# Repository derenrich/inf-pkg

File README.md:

# E-Ink RP2040 Driver Board with weird extras

View it at [kicanvas](https://kicanvas.org/?repo=https%3A%2F%2Fgithub.com%2Fderenrich%2Finf-pkg).

# Based off of RP2040 Minimal Design for JLCPCB
Based on [Minimal design example](https://datasheets.raspberrypi.com/rp2040/Minimal-KiCAD.zip) referenced in [Hardware design with RP2040: Using RP2040 microcontrollers to build boards and products](https://datasheets.raspberrypi.com/rp2040/hardware-design-with-rp2040.pdf).  Design updated for KiCAD 7 and manufacture/assembly at JLCPCB.

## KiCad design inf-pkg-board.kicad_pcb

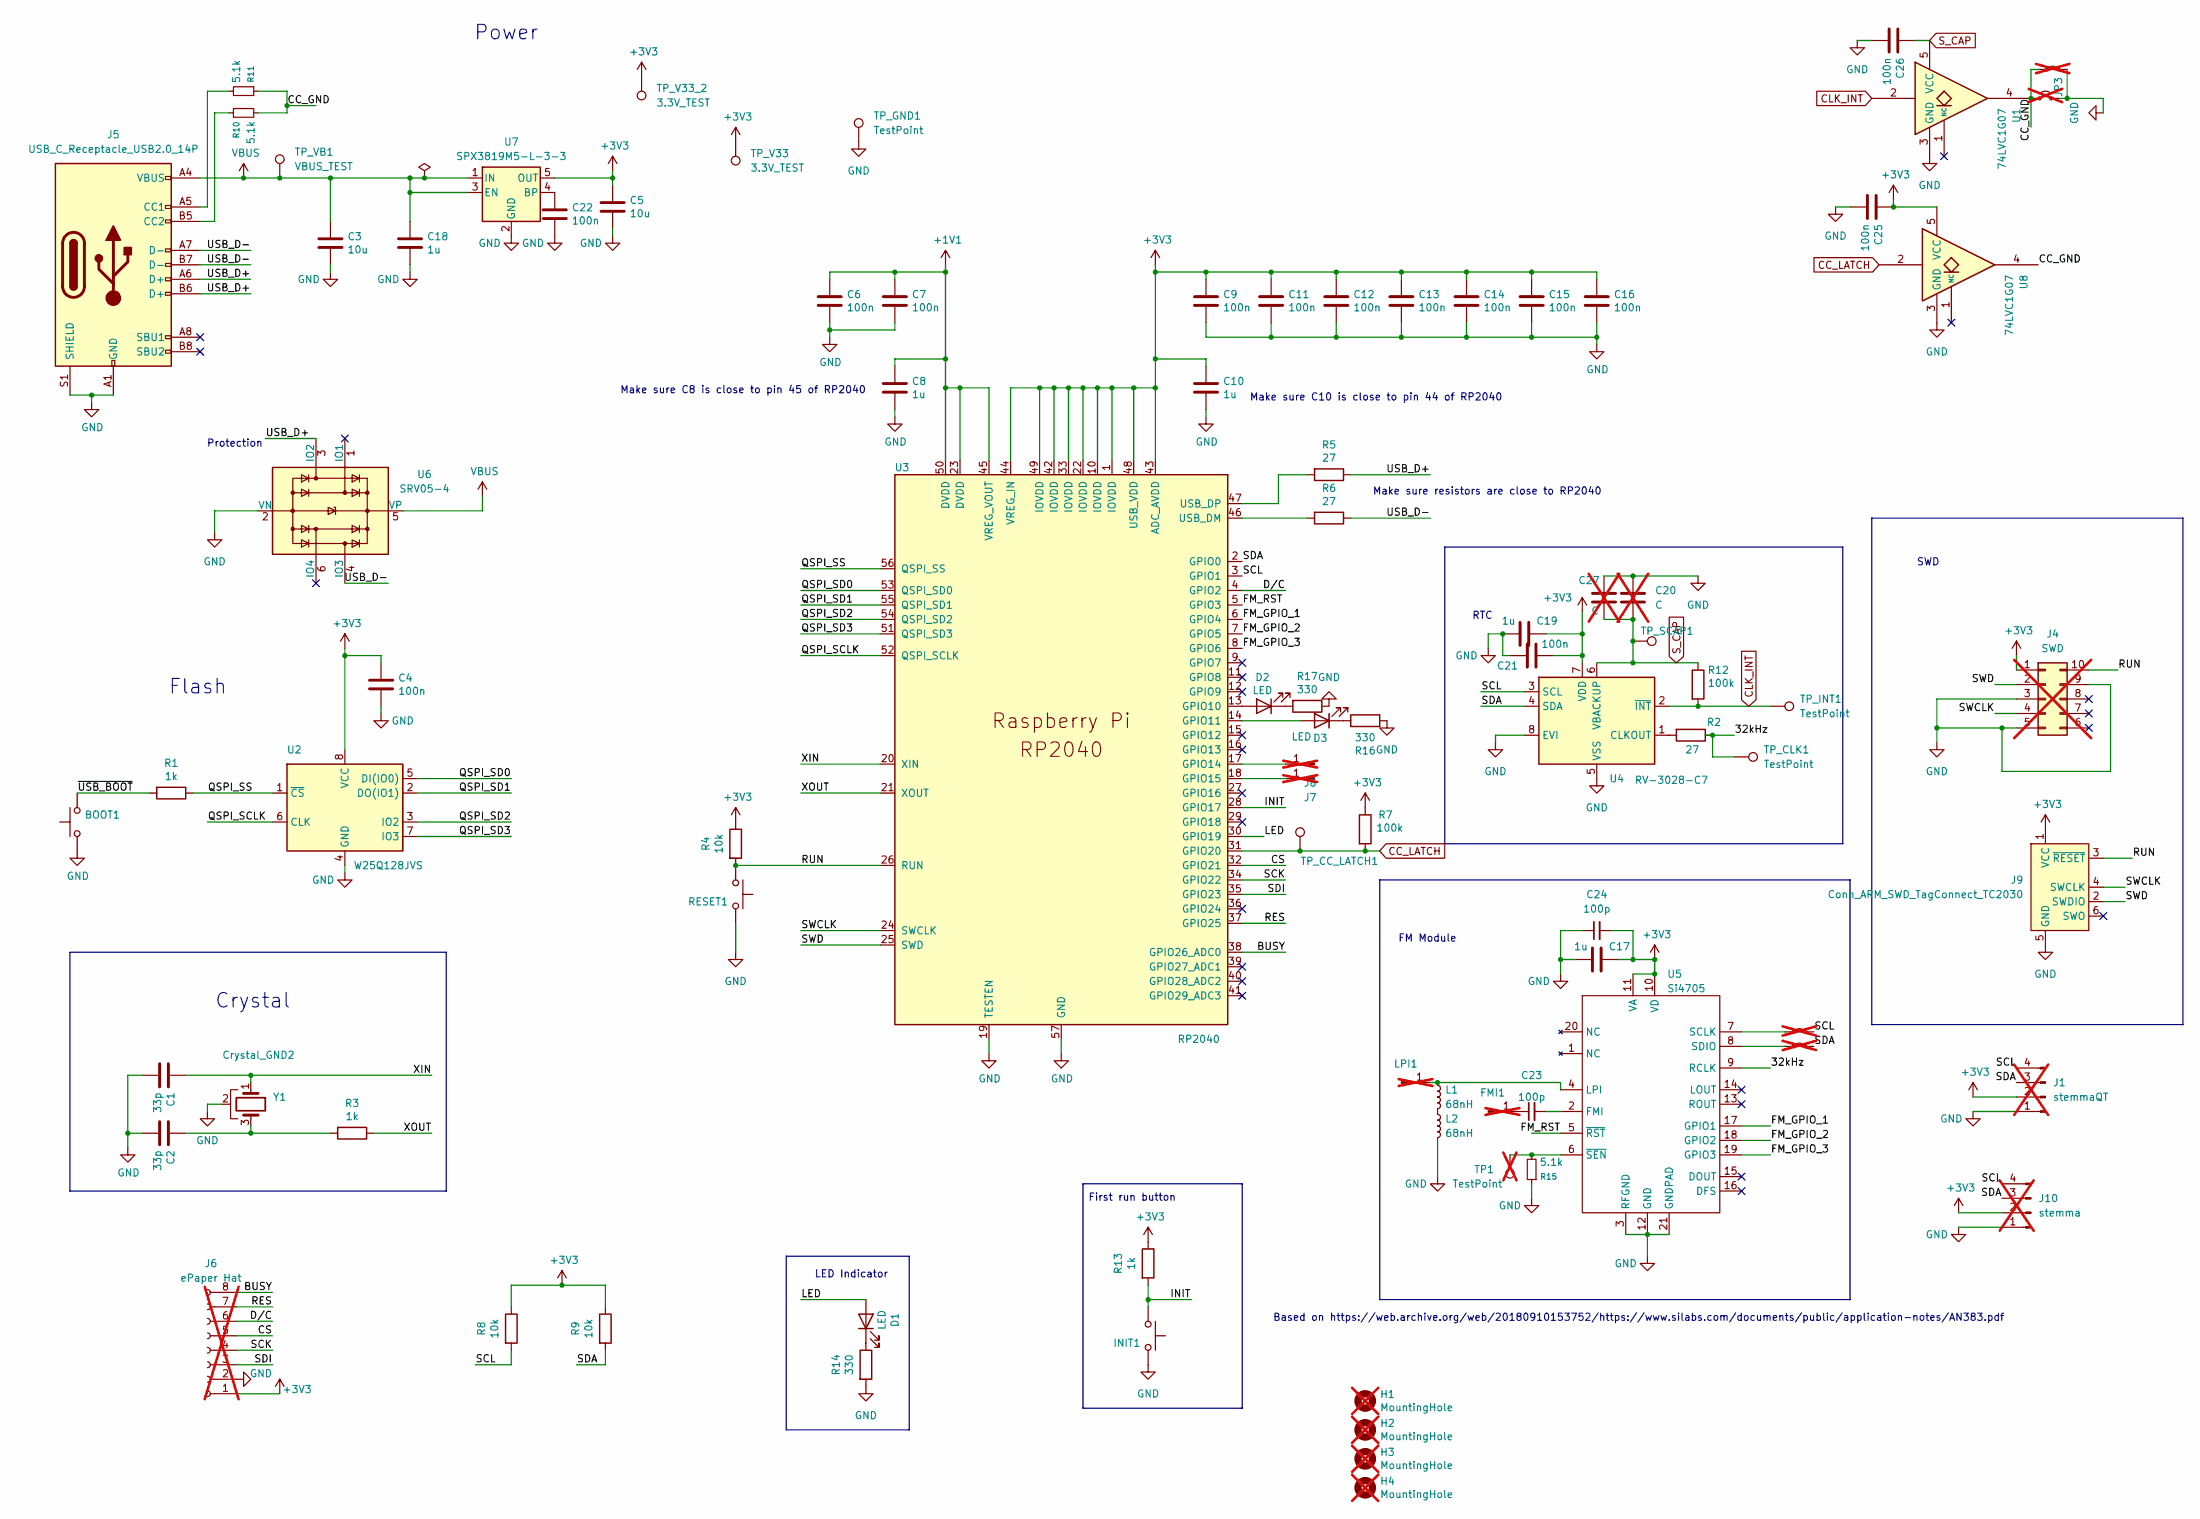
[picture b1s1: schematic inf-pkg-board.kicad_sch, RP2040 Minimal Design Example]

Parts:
BOOT1: TS-1088-AR02016; LCSC C720477
C1, C2: 33p; C_0402_1005Metric; LCSC C1562
C3, C5: 10u; C_0805_2012Metric; LCSC C15850
C4, C6, C7, C9, C11, C12, C13, C14, C15, C16, C21, C22, C25, C26: 100n; C_0402_1005Metric; LCSC C1525
C8, C10, C17, C18, C19: 1u; C_0402_1005Metric; LCSC C52923
C20: C; C_R21.00mm_P6.00mm; not fitted
C23, C24: 100p; C_0402_1005Metric; LCSC C1546
C27: C; C_Disc_D16.0mm_W5.0mm_P10.00mm; not fitted
D1, D2, D3: LED; D_0805_2012Metric; LCSC C84256
FMI1: Conn_01x01_Pin; PinHeader_1x01_P1.00mm_Vertical; not fitted
H1, H2, H3, H4: MountingHole; MountingHole_2.7mm_M2.5; not fitted
INIT1: TS-1088-AR02016; LCSC C720477
J1: stemmaQT; JST_PH_S4B-PH-K_1x04_P2.00mm_Horizontal; not fitted
J4: SWD; PinHeader_2x05_P1.27mm_Vertical_SMD; not fitted
J5: USB_C_Receptacle_USB2.0_14P; USB_C_Receptacle_G-Switch_GT-USB-7010ASV; LCSC C2988369
J6: ePaper Hat; PinHeader_1x08_P2.54mm_Vertical; not fitted
J7, J8: Conn_01x01_Pin; PinHeader_1x01_P2.54mm_Vertical; not fitted
J9: Conn_ARM_SWD_TagConnect_TC2030; Tag-Connect_TC2030-IDC-FP_2x03_P1.27mm_Vertical
J10: stemma; JST_PH_B4B-PH-K_1x04_P2.00mm_Vertical; not fitted
JP1, JP2: Jumper_2_Small_Bridged; SolderJumper-2_P1.3mm_Bridged_Pad1.0x1.5mm; not fitted
JP3: Jumper_2_Small_Open; PinHeader_1x02_P2.54mm_Vertical; not fitted
JP4: Jumper_2_Small_Bridged; SolderJumper-2_P1.3mm_Open_TrianglePad1.0x1.5mm; not fitted
L1, L2: 68nH; L_0603_1608Metric; LCSC C13415
LPI1: Conn_01x01_Pin; PinHeader_1x01_P2.54mm_Vertical; not fitted
R1, R3, R13: 1k; R_0402_1005Metric; LCSC C11702
R2, R5, R6: 27; R_0603_1608Metric; LCSC C25190
R4, R8, R9: 10k; R_0805_2012Metric; LCSC C17414
R7, R12: 100k; R_0402_1005Metric; LCSC C25741
R10, R11, R15: 5.1k; R_0402_1005Metric; LCSC C25905
R14, R16, R17: 330; R_0402_1005Metric; LCSC C25104
RESET1: TS-1088-AR02016; LCSC C720477
TP1: TestPoint; PinHeader_1x01_P1.00mm_Vertical; not fitted
TP_CC_LATCH1: TestPoint; TestPoint_Pad_D1.5mm
TP_CLK1: TestPoint; TestPoint_Pad_D1.5mm
TP_GND1: TestPoint; TestPoint_Pad_D1.5mm
TP_INT1: TestPoint; TestPoint_Pad_D1.5mm
TP_SCAP1: TestPoint; TestPoint_Pad_D2.5mm
TP_V33, TP_V33_2: 3.3V_TEST; TestPoint_Pad_D2.0mm
TP_VB1: VBUS_TEST; TestPoint_Pad_D2.0mm
U1, U8: 74LVC1G07; SOT-353_SC-70-5; LCSC C282345
U2: W25Q128JVS; SOIC-8_5.23x5.23mm_P1.27mm; LCSC C97521
U3: RP2040; RP2040-QFN-56; LCSC C2040
U4: RV-3028-C7; MicroCrystal_C7_SON-8_1.5x3.2mm_P0.9mm; LCSC C3019759
U5: Si4705; SiliconLabs_QFN-20-1EP_3x3mm_P0.5mm_EP1.8x1.8mm; LCSC C1526114
U6: SRV05-4; SOT-23-6; LCSC C85364
U7: SPX3819M5-L-3-3; SOT-23-5; LCSC C9055
Y1: Crystal_GND2; Crystal_SMD_3225-4Pin_3.2x2.5mm; LCSC C9002

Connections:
+1V1: C6.1, C7.1, C8.1, U3.23 (DVDD), U3.45 (VREG_VOUT), U3.50 (DVDD)
+3V3: C4.1, C5.1, C9.1, C10.1, C11.1, C12.1, C13.1, C14.1, C15.1, C16.1, C17.1, C19.1, C21.2, C24.2, C25.1, J1.2, J4.1, J6.1, J9.1 (VCC), J10.2, R4.1, R7.1, R8.1, R9.1, R13.1, TP_V33.1, TP_V33_2.1, U2.8 (VCC), U3.1 (IOVDD), U3.10 (IOVDD), U3.22 (IOVDD), U3.33 (IOVDD), U3.42 (IOVDD), U3.43 (ADC_AVDD), U3.44 (VREG_IN), U3.48 (USB_VDD), U3.49 (IOVDD), U4.7 (VDD), U5.10 (VD), U5.11 (VA), U7.5 (OUT), U8.5 (VCC)
/32kHz: R2.1, TP_CLK1.1, U5.9 (RCLK)
/BUSY: J6.8, U3.38 (GPIO26_ADC0)
/CC_GND: JP3.1 (A), JP4.1 (A), R10.2, R11.1, U1.4, U8.4
/CS: J6.5, U3.32 (GPIO21)
/D/C: J6.6, U3.4 (GPIO2)
/FM_GPIO_1: U3.6 (GPIO4), U5.17 (GPIO1)
/FM_GPIO_2: U3.7 (GPIO5), U5.18 (GPIO2)
/FM_GPIO_3: U3.8 (GPIO6), U5.19 (GPIO3)
/FM_RST: U3.5 (GPIO3), U5.5 (~RST)
/INIT: INIT1.1, R13.2, U3.28 (GPIO17)
/LED: D1.2 (A), U3.30 (GPIO19)
/QSPI_SCLK: U2.6 (CLK), U3.52 (QSPI_SCLK)
/QSPI_SD0: U2.5 (DI(IO0)), U3.53 (QSPI_SD0)
/QSPI_SD1: U2.2 (DO(IO1)), U3.55 (QSPI_SD1)
/QSPI_SD2: U2.3 (IO2), U3.54 (QSPI_SD2)
/QSPI_SD3: U2.7 (IO3), U3.51 (QSPI_SD3)
/QSPI_SS: R1.1, U2.1 (~CS), U3.56 (QSPI_SS)
/RES: J6.7, U3.37 (GPIO25)
/RUN: J4.10, J9.3 (~RESET), R4.2, RESET1.1, U3.26 (RUN)
/SCK: J6.4, U3.34 (GPIO22)
/SCL: J1.4, J10.4, JP1.2 (B), R8.2, U3.3 (GPIO1), U4.3 (SCL)
/SDA: J1.3, J10.3, JP2.2 (B), R9.2, U3.2 (GPIO0), U4.4 (SDA)
/SDI: J6.3, U3.35 (GPIO23)
/SWCLK: J4.4, J9.4 (SWCLK), U3.24 (SWCLK)
/SWD: J4.2, J9.2 (SWDIO), U3.25 (SWD)
/USB_D+: J5.A6 (D+), J5.B6 (D+), R5.1, U6.3 (IO2)
/USB_D-: J5.A7 (D-), J5.B7 (D-), R6.1, U6.4 (IO3)
/XIN: C1.1, U3.20 (XIN), Y1.1
/XOUT: R3.1, U3.21 (XOUT)
/~USB_BOOT: BOOT1.2, R1.2
CC_LATCH: R7.2, TP_CC_LATCH1.1, U3.31 (GPIO20), U8.2
CLK_INT: R12.2, TP_INT1.1, U1.2, U4.2 (~INT)
GND: BOOT1.1, C1.2, C2.2, C3.2, C4.2, C5.2, C6.2, C7.2, C8.2, C9.2, C10.2, C11.2, C12.2, C13.2, C14.2, C15.2, C16.2, C17.2, C18.2, C19.2, C20.1, C21.1, C22.2, C24.1, C25.2, C26.2, C27.1, INIT1.2, J1.1, J4.3, J4.5, J4.9, J5.A1 (GND), J5.A12 (GND), J5.B1 (GND), J5.B12 (GND), J5.S1 (SHIELD), J6.2, J9.5 (GND), J10.1, JP3.2 (B), JP4.2 (B), L2.2, R14.2, R15.1, R16.2, R17.1, RESET1.2, TP_GND1.1, U1.3 (GND), U2.4 (GND), U3.19 (TESTEN), U3.57 (GND), U4.5 (VSS), U4.8 (EVI), U5.3 (RFGND), U5.12 (GND), U5.21 (GNDPAD), U6.2 (VN), U7.2 (GND), U8.3 (GND), Y1.2
unnamed: C2.1, R3.2, Y1.3
unnamed: D1.1 (K), R14.1
unnamed: D2.2 (A), U3.13 (GPIO10)
unnamed: D2.1 (K), R17.2
unnamed: D3.2 (A), U3.14 (GPIO11)
unnamed: D3.1 (K), R16.1
unnamed: C23.1, FMI1.1
unnamed: J5.A5 (CC1), R11.2
unnamed: J5.B5 (CC2), R10.1
unnamed: J7.1, U3.18 (GPIO15)
unnamed: J8.1, U3.17 (GPIO14)
unnamed: JP1.1 (A), U5.7 (SCLK)
unnamed: JP2.1 (A), U5.8 (SDIO)
unnamed: L1.2, L2.1
unnamed: L1.1, LPI1.1, U5.4 (LPI)
unnamed: R6.2, U3.46 (USB_DM)
unnamed: R5.2, U3.47 (USB_DP)
unnamed: R2.2, U4.1 (CLKOUT)
unnamed: C23.2, U5.2 (FMI)
unnamed: R15.2, TP1.1, U5.6 (~SEN)
unnamed: C22.1, U7.4 (BP)
S_CAP: C20.2, C26.1, C27.2, R12.1, TP_SCAP1.1, U1.5 (VCC), U4.6 (VBACKUP)
VBUS: C3.1, C18.1, J5.A4 (VBUS), J5.A9 (VBUS), J5.B4 (VBUS), J5.B9 (VBUS), TP_VB1.1, U6.5 (VP), U7.1 (IN), U7.3 (EN)

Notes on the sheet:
First run button
FM Module
Make sure C8 is close to pin 45 of RP2040
SWD
Protection
Make sure C10 is close to pin 44 of RP2040
Crystal
Power
RTC
Based on https://web.archive.org/web/20180910153752/https://www.silabs.com/documents/public/application-notes/AN383.pdf
Flash
Make sure resistors are close to RP2040
LED Indicator

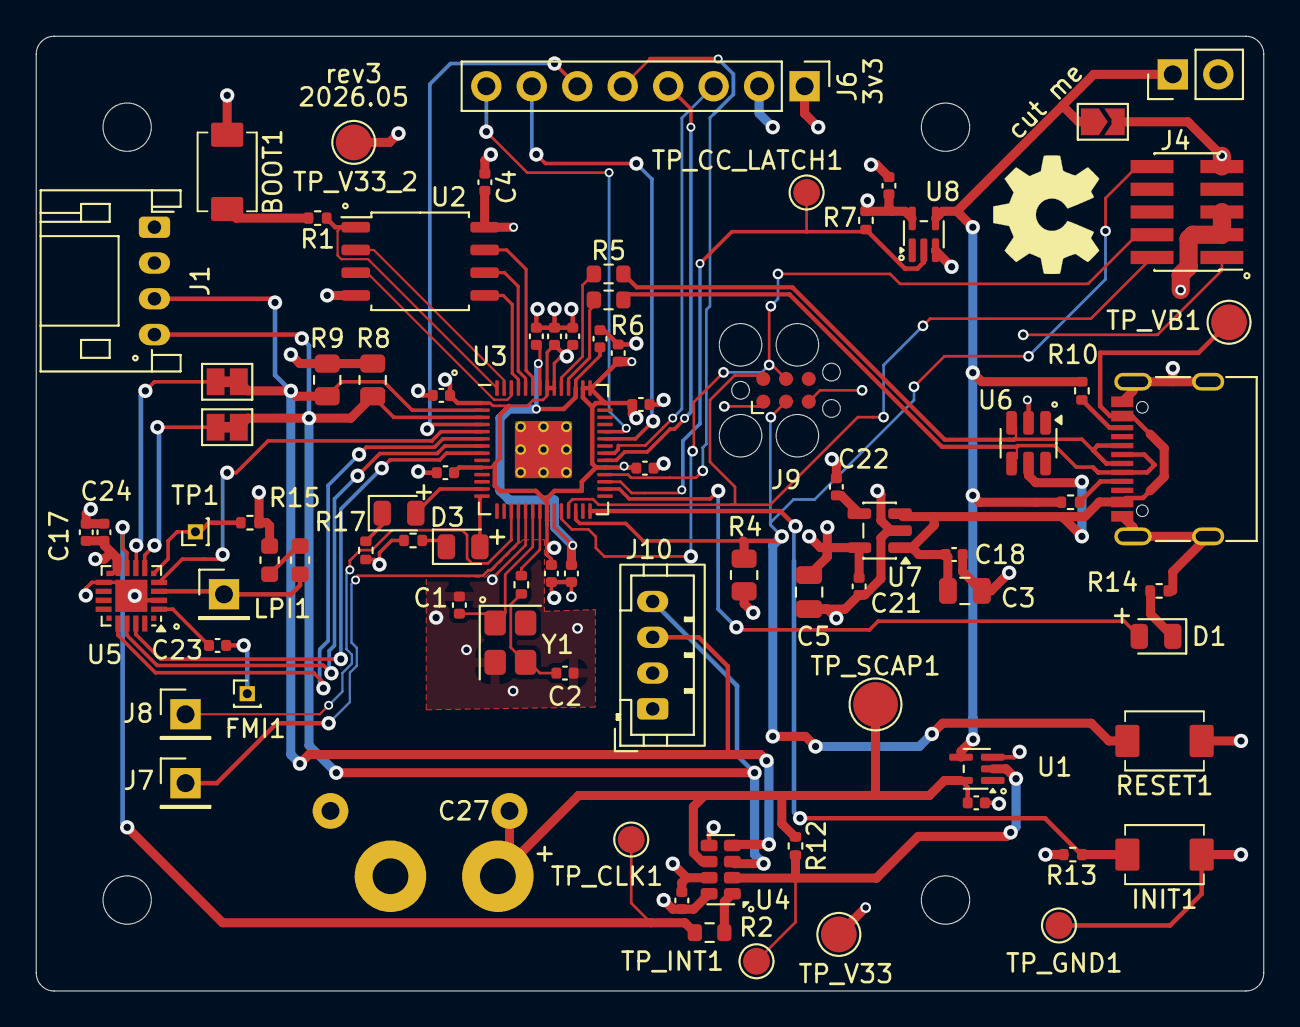
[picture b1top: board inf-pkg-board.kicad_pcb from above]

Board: 4 copper layers, 68.6 x 53.3 mm, 88 parts (1 on the bottom side), 58 nets.

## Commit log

2026-02-14 my version
2026-02-14 cleanup
2026-02-16 fixes
2026-03-28 fix bom error / add debug pads
2026-03-29 bom optimization
2026-03-29 bump readme
2026-03-29 typo
2026-03-29 more ground
2026-04-01 final tweaks
2026-04-01 swap resistor to smaller/standard size
2026-05-13 check
